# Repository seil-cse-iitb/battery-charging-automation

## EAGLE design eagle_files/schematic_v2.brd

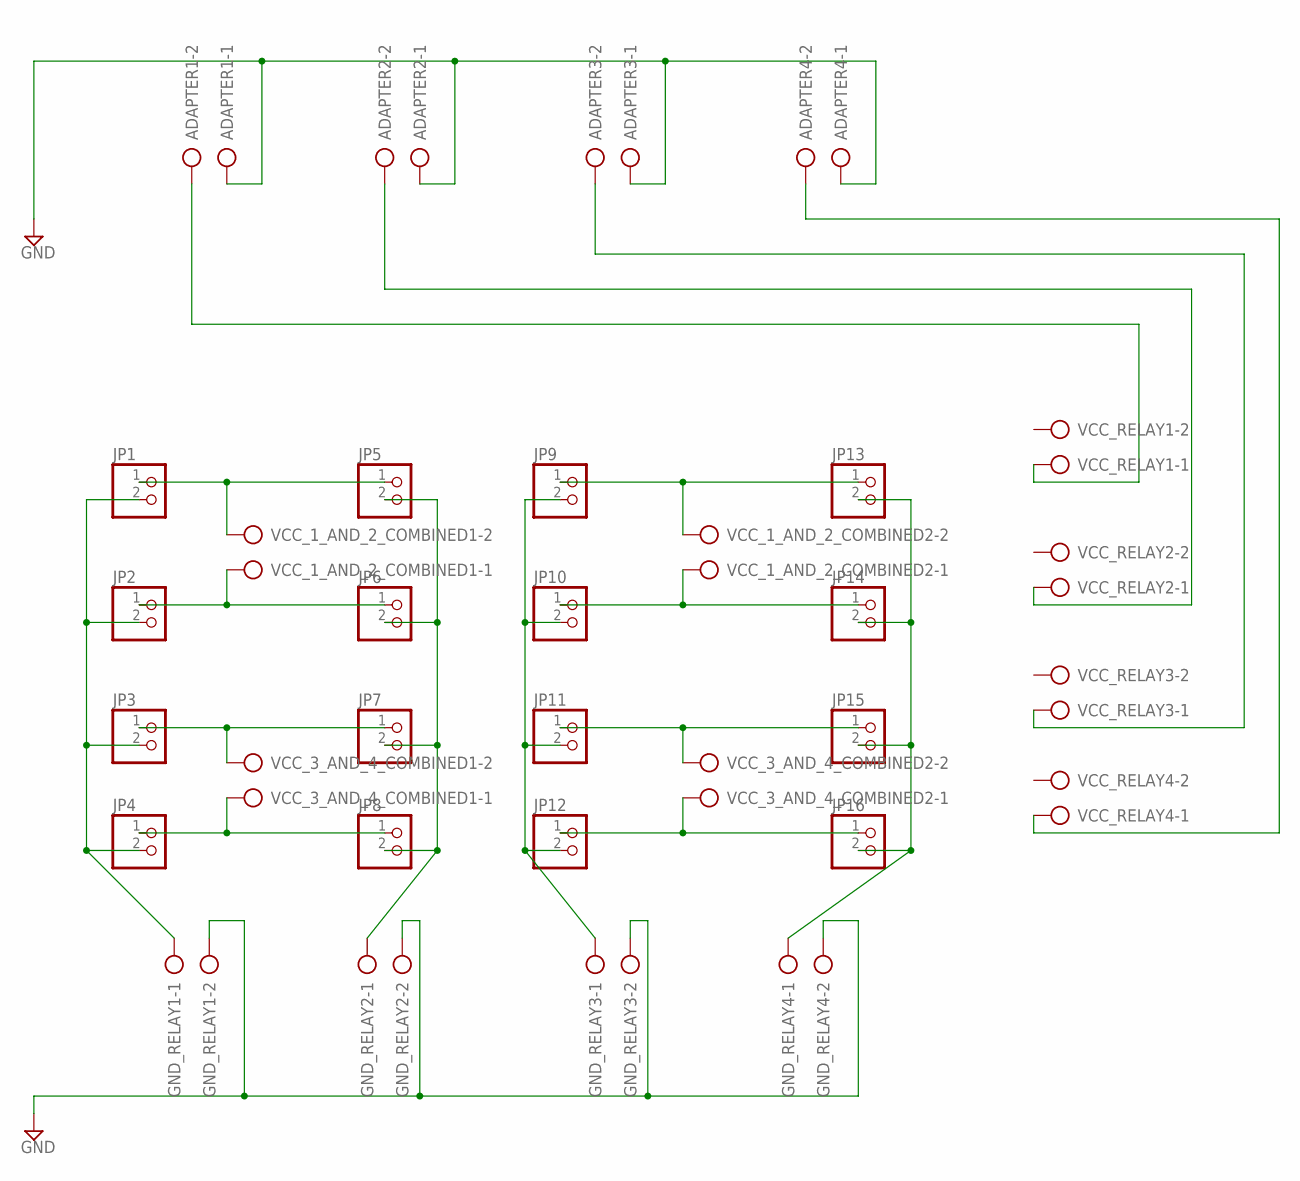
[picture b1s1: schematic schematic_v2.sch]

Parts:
ADAPTER1, ADAPTER2, ADAPTER3, ADAPTER4: AK300/2
GND_RELAY1, GND_RELAY2, GND_RELAY3, GND_RELAY4: AK300/2
JP1, JP2, JP3, JP4, JP5, JP6, JP7, JP8, JP9, JP10, JP11, JP12, JP13, JP14, JP15, JP16: PINHD-1X2; 1X02
VCC_1_AND_2_COMBINED1, VCC_1_AND_2_COMBINED2, VCC_3_AND_4_COMBINED1, VCC_3_AND_4_COMBINED2: AK300/2
VCC_RELAY1, VCC_RELAY2, VCC_RELAY3, VCC_RELAY4: AK300/2

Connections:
GND: ADAPTER1.1, ADAPTER2.1, ADAPTER3.1, ADAPTER4.1, GND_RELAY1.2, GND_RELAY2.2, GND_RELAY3.2, GND_RELAY4.2
unnamed: JP1.1, JP5.1, VCC_1_AND_2_COMBINED1.2
unnamed: JP2.1, JP6.1, VCC_1_AND_2_COMBINED1.1
unnamed: JP3.1, JP7.1, VCC_3_AND_4_COMBINED1.2
unnamed: JP4.1, JP8.1, VCC_3_AND_4_COMBINED1.1
unnamed: ADAPTER1.2, VCC_RELAY1.1
unnamed: ADAPTER4.2, VCC_RELAY4.1
unnamed: GND_RELAY1.1, JP1.2, JP2.2, JP3.2, JP4.2
unnamed: GND_RELAY2.1, JP5.2, JP6.2, JP7.2, JP8.2
unnamed: GND_RELAY3.1, JP9.2, JP10.2, JP11.2, JP12.2
unnamed: GND_RELAY4.1, JP13.2, JP14.2, JP15.2, JP16.2
unnamed: ADAPTER3.2, VCC_RELAY3.1
unnamed: ADAPTER2.2, VCC_RELAY2.1
unnamed: JP9.1, JP13.1, VCC_1_AND_2_COMBINED2.2
unnamed: JP10.1, JP14.1, VCC_1_AND_2_COMBINED2.1
unnamed: JP11.1, JP15.1, VCC_3_AND_4_COMBINED2.2
unnamed: JP12.1, JP16.1, VCC_3_AND_4_COMBINED2.1

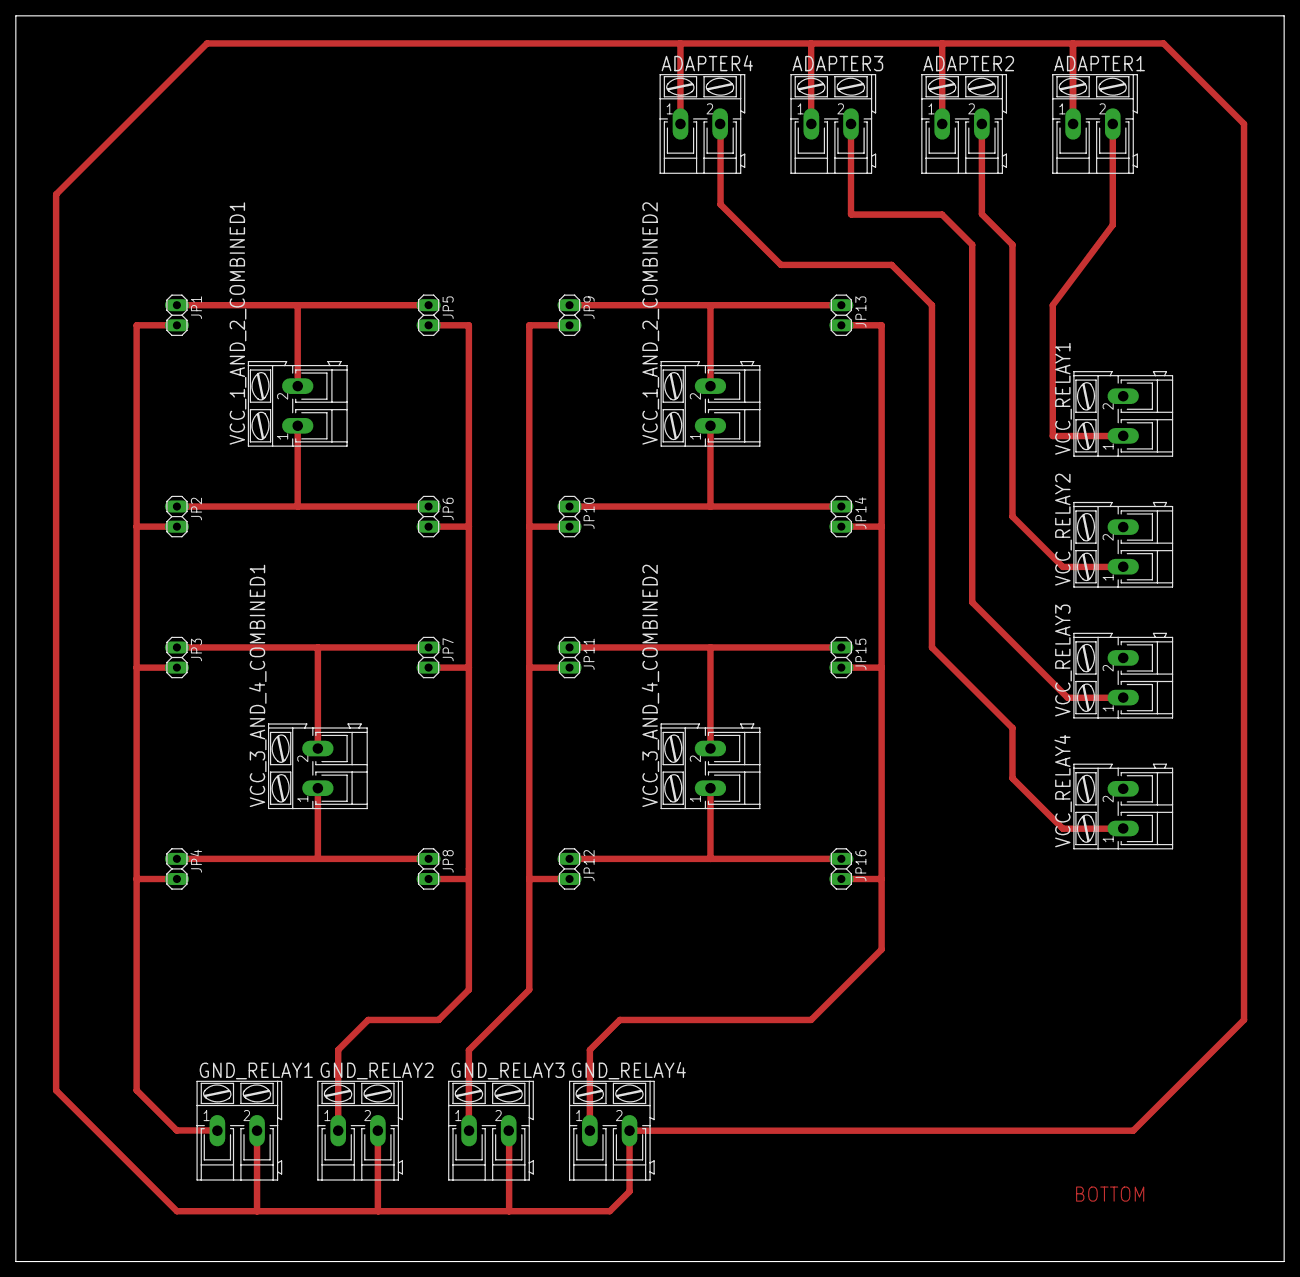
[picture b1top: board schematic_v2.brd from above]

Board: 2 copper layers, 160.0 x 157.2 mm, 32 parts (0 on the bottom side), 17 nets.

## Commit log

2017-08-09 Adding Battery-charging-automation pcb and code
2017-08-09 Add license
